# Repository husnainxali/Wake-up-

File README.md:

# Wake_up
An alarm clock based on the retro brick phone customized for your own prefrence and style.

## Description

This is a custom alarm clock that I made.
While I was scrolling Pinterest I saw an old 90s brick phone and I got the idea to make an alarm clock for my room that looks like an brick phone although its not as polished as my imagination but as a beginner it has been a great project for me.
I learned a lot from this project and i am looking forward to make it better. 

### Screenshots
- Schematics

- PCB

- Case

## Getting Started

- I created the schematics ,pcb layout and routing from scratch in KIcad
- I used Fusion 360 to make the CAD model for the alarm clock it took a lot of time to design the 3d model i had to restart 2 times because i made changes on pcb that couldnt fit into the previous model   

## Install 
- Download PCB Files
- Download Arduino IDE
- Install ESP32 board on Arduino IDE
- Download Firmware file

### Dependencies

#Libraries
- Adafruit GFX Library
- Adafruit ST7735 and ST7789 Library

### Executing program

- Open Arduino IDE
- Open *[alarm_Firmware.ino](Firmware/alarm_Firmware.ino)*
- Flash the firmware to ESP32 C3

### How it works

The XIAO ESP32-C3 connects to WiFi and downloads the time. The six buttons are wired in a matrix, and the firmware reads them to change the alarm hour and minute. Before flashing, open the firmware file and type in your own WiFi name and password.

## License

This project is licensed under the MIT License - see the *[LICENSE](LICENSE)*

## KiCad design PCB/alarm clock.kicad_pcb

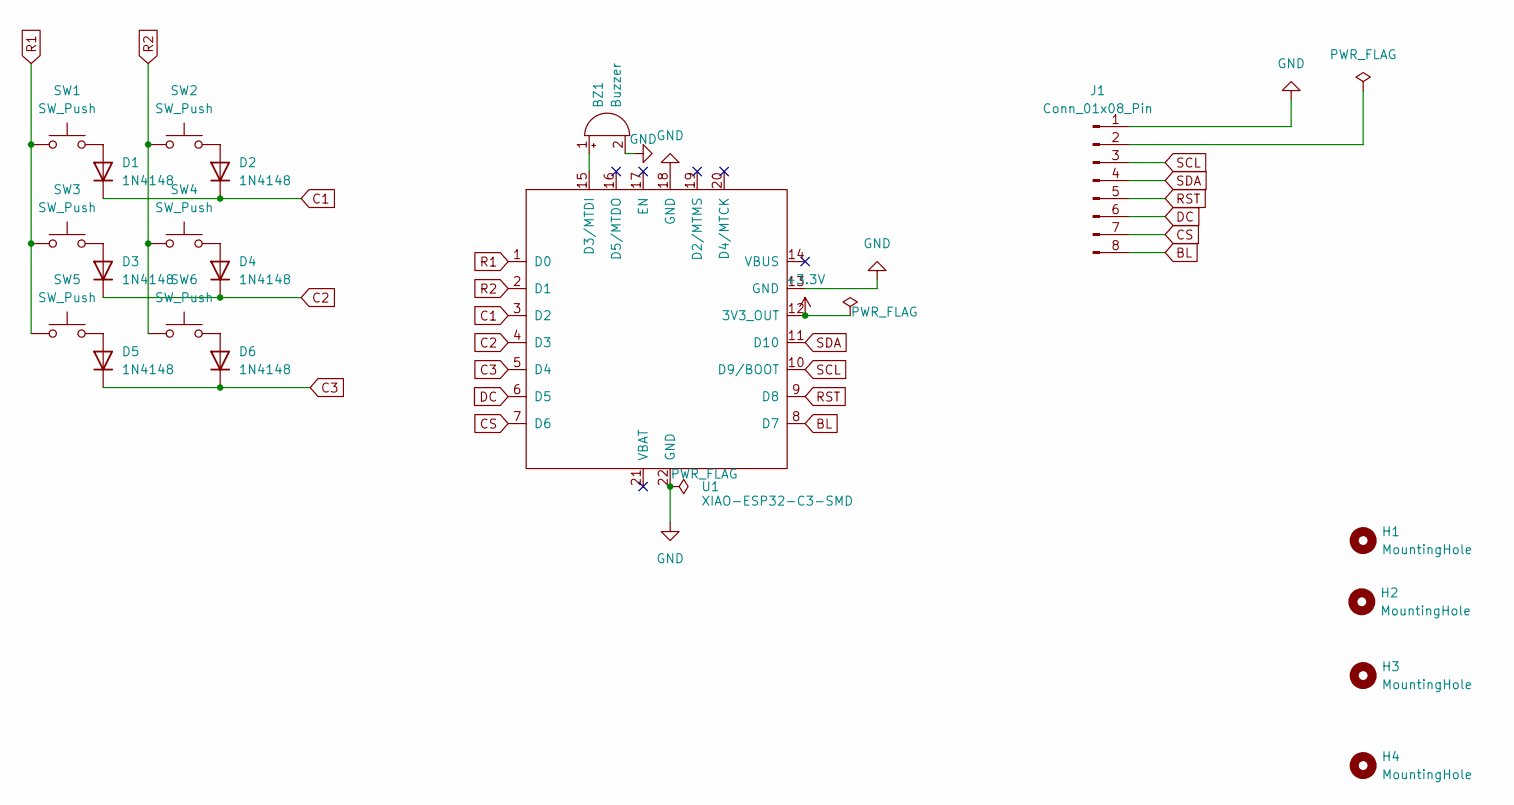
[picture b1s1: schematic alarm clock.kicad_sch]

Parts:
BZ1: Buzzer; Buzzer_12x9.5RM7.6
D1, D2, D3, D4, D5, D6: 1N4148; D_DO-35_SOD27_P7.62mm_Horizontal
H1, H2, H3, H4: MountingHole; MountingHole_3.2mm_M3
J1: Conn_01x08_Pin; PinSocket_1x08_P2.54mm_Vertical
SW1, SW2, SW3, SW4, SW5, SW6: SW_Push; SW_Cherry_MX_1.00u_PCB
U1: XIAO-ESP32-C3-SMD; MCU_Seeed_ESP32C3

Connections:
+3.3V: U1.12 (3V3_OUT)
BL: J1.8, U1.8 (D7)
C1: D1.1 (K), D2.1 (K), U1.3 (D2)
C2: D3.1 (K), D4.1 (K), U1.4 (D3)
C3: D5.1 (K), D6.1 (K), U1.5 (D4)
CS: J1.7, U1.7 (D6)
DC: J1.6, U1.6 (D5)
GND: BZ1.2 (-), J1.1, U1.13 (GND), U1.18 (GND), U1.22 (GND)
unnamed: BZ1.1 (+), U1.15 (D3/MTDI)
unnamed: D1.2 (A), SW1.2
unnamed: D2.2 (A), SW2.2
unnamed: D3.2 (A), SW3.2
unnamed: D4.2 (A), SW4.2
unnamed: D5.2 (A), SW5.2
unnamed: D6.2 (A), SW6.2
R1: SW1.1, SW3.1, SW5.1, U1.1 (D0)
R2: SW2.1, SW4.1, SW6.1, U1.2 (D1)
RST: J1.5, U1.9 (D8)
SCL: J1.3, U1.10 (D9/BOOT)
SDA: J1.4, U1.11 (D10)

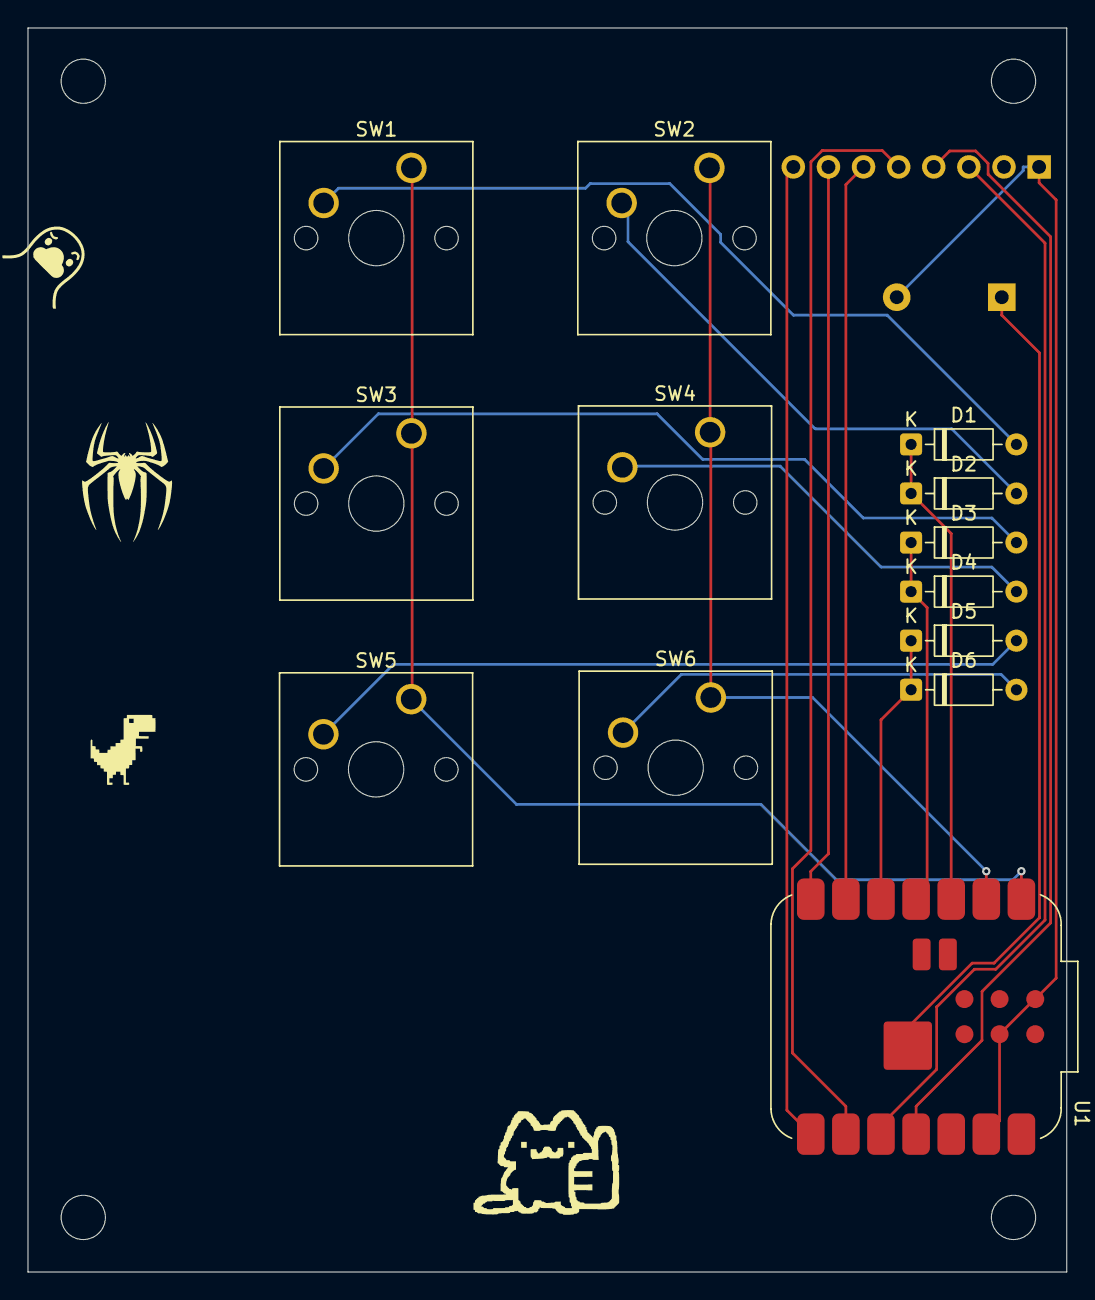
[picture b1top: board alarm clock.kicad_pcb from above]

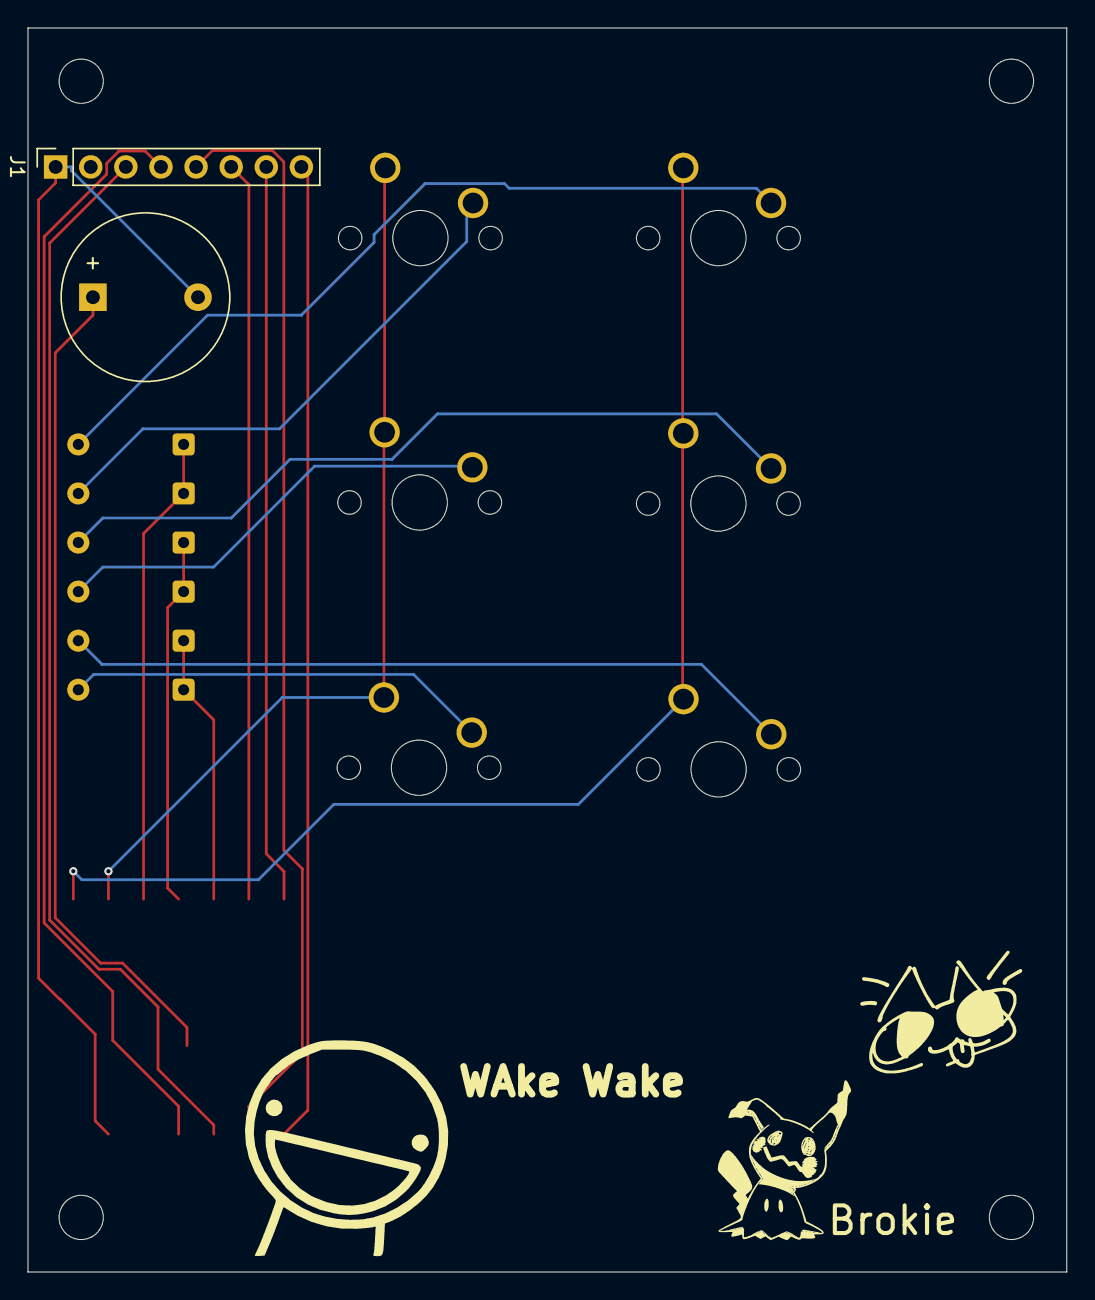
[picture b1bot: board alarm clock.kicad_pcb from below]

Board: 2 copper layers, 75.2 x 90.0 mm, 19 parts (2 on the bottom side), 19 nets.

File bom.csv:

Item,Reference,Description,Quantity,Notes
Microcontroller,U1,Seeed Studio XIAO ESP32-C3,1,Main controller with WiFi
Display,-,8-pin SPI TFT display module (ST7789 1.14" 135x240),1,Plugs into J1; confirm exact model
Mechanical switch,SW1-SW6,MX-style mechanical keyboard switch,6,Soldered to PCB
Keycap,-,MX-style keycap,6,One per switch
Diode,D1-D6,1N4148 through-hole diode,6,One per switch for the key matrix
Buzzer,BZ1,Piezo buzzer (through-hole),1,Connected to D3 and GND; confirm passive or active
Pin header,J1,1x08 2.54mm header (female socket),1,Display connection
Screw,H1-H4,M3 screw,4,PCB mounting holes; confirm length used with your case
PCB,-,Custom PCB (KiCad),1,Order from your PCB manufacturer
Case,-,3D printed brick phone case (Fusion 360),1,Printed in PLA or similar
USB-C cable,-,USB-C cable for power and flashing,1,Not included on the PCB
